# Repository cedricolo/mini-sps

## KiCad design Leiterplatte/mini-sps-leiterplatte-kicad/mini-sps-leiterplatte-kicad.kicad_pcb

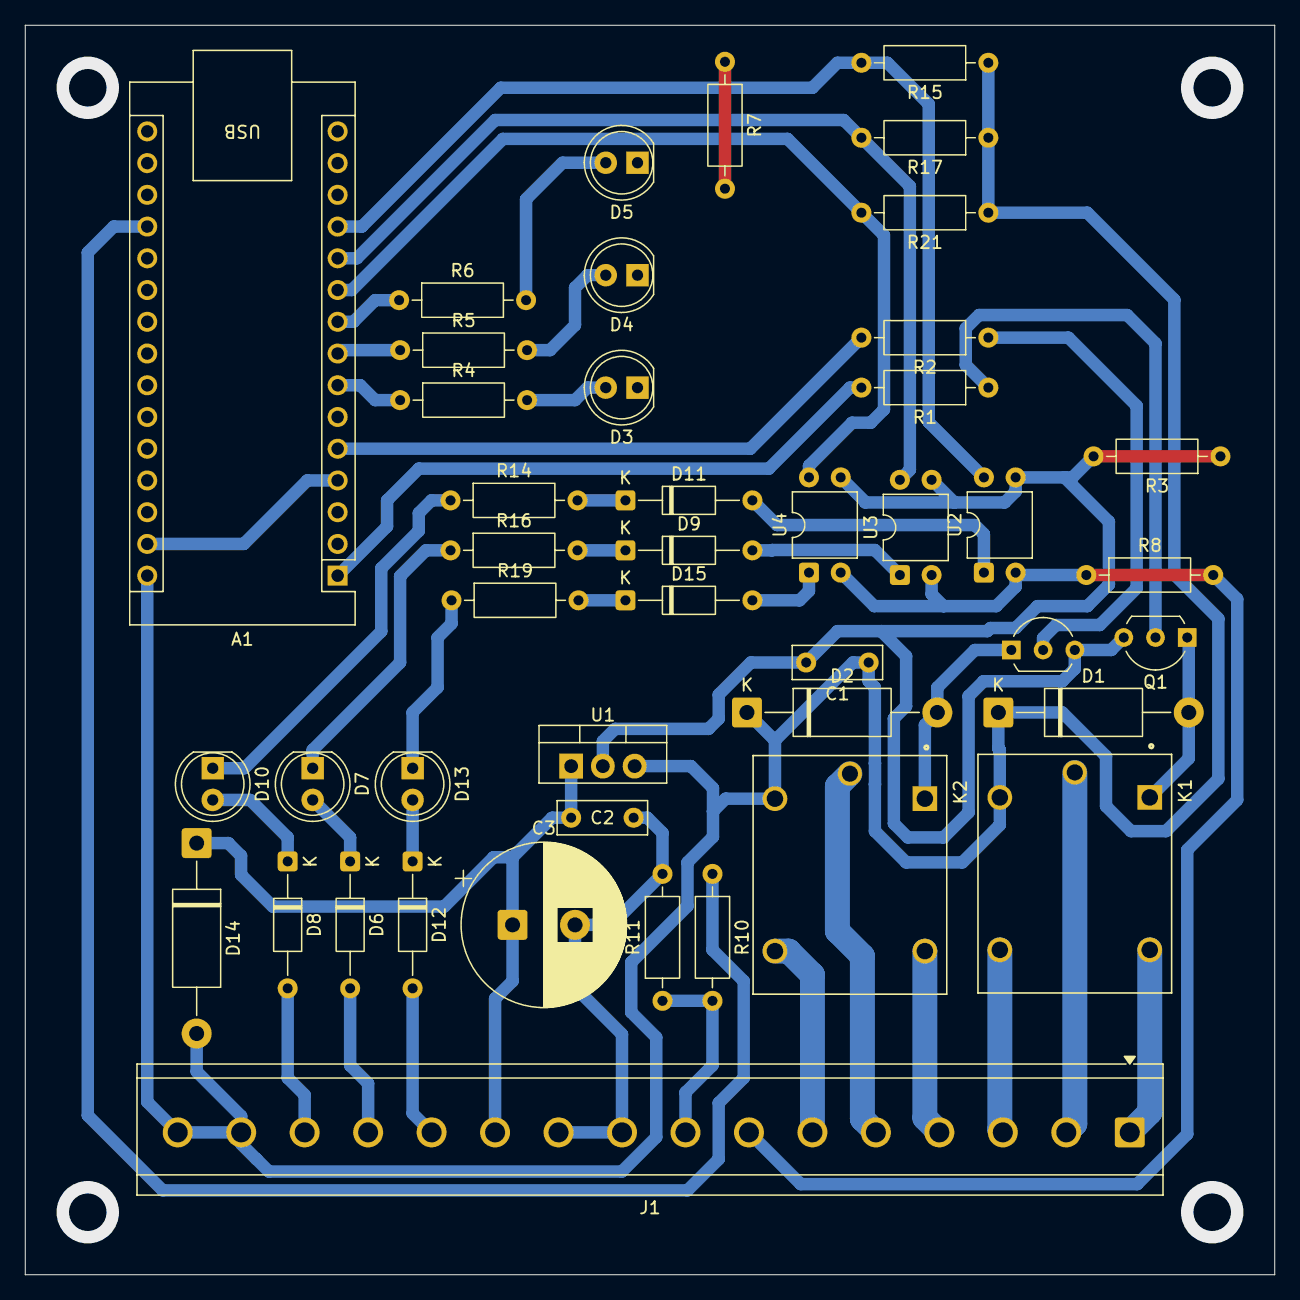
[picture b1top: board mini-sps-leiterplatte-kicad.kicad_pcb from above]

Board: 2 copper layers, 100.0 x 100.0 mm, 44 parts (0 on the bottom side), 42 nets.

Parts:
A1: Arduino_Nano_v3.x; Arduino_Nano
C1: 100nF; C_Disc_D7.0mm_W2.5mm_P5.00mm
C2: 330 nF; C_Disc_D7.0mm_W2.5mm_P5.00mm
C3: 10uF; CP_Radial_D13.0mm_P5.00mm
D1, D2, D14: 1N4007; D_DO-15_P15.24mm_Horizontal
D3, D4, D5, D7, D10, D13: LED; LED_D5.0mm
D6, D8, D12: 1N4148WT; D_DO-35_SOD27_P10.16mm_Horizontal
D9, D11, D15: BZV55B5V1; D_DO-35_SOD27_P10.16mm_Horizontal
J1: Screw_Terminal_01x16; TerminalBlock_CUI_TB007-508-16_1x16_P5.08mm_Horizontal
K1, K2: SRD-05VDC-SL-C; RELAY_SRD-05VDC-SL-C
Q1, Q2: BC547; TO-92L_Inline_Wide
R1, R2: 1k; R_Axial_DIN0207_L6.3mm_D2.5mm_P10.16mm_Horizontal
R3, R7, R8: 0; R_Axial_DIN0207_L6.3mm_D2.5mm_P10.16mm_Horizontal
R4, R5, R6: 330; R_Axial_DIN0207_L6.3mm_D2.5mm_P10.16mm_Horizontal
R10: 39k; R_Axial_DIN0207_L6.3mm_D2.5mm_P10.16mm_Horizontal
R11, R15, R17, R21: 10k; R_Axial_DIN0207_L6.3mm_D2.5mm_P10.16mm_Horizontal
R14, R16, R19: 1500; R_Axial_DIN0207_L6.3mm_D2.5mm_P10.16mm_Horizontal
U1: L7805; TO-220-3_Vertical
U2, U3, U4: PC817; DIP-4_W7.62mm

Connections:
+5V: A1.30 (VIN), C1.1, D1.1 (K), D2.1 (K), D14.2 (A), J1.15, J1.16, K1.A2, K2.A2, R15.1, R17.1, R21.1, U1.3 (OUT)
A0: A1.19 (A0), R10.1
AIN 1: J1.8, R10.2, R11.1
COM1: J1.2, K1.COM
COM2: J1.5, K2.COM
D1: A1.1 (D1/TX), R1.2
D2: A1.5 (D2), R2.2
D4(R): A1.7 (D4), R4.1
D5(G): A1.8 (D5), R5.1
D6(B): A1.9 (D6), R6.1
D7: A1.10 (D7), R21.2, U4.4
D8: A1.11 (D8), R17.2, U3.4
D9: A1.12 (D9), R15.2, U2.4
DI1: D12.2 (A), J1.12
DI2: D6.2 (A), J1.13
DI3: D8.2 (A), J1.14
GND: A1.4 (GND), A1.29 (GND), C1.2, C2.2, C3.2, D3.1 (K), D4.1 (K), D5.1 (K), J1.9, J1.10, Q1.3 (E), Q2.3 (E), R3.1, R3.2, R7.1, R7.2, R11.2, U1.2 (GND), U2.3, U3.3, U4.3
GND1: J1.7, R8.1, R8.2, U2.2, U3.2, U4.2
NC 1: J1.1, K1.NC
NC 2: J1.4, K2.NC
NO 1: J1.3, K1.NO
NO 2: J1.6, K2.NO
unnamed: D1.2 (A), K1.A1, Q1.1 (C)
unnamed: D2.2 (A), K2.A1, Q2.1 (C)
unnamed: D3.2 (A), R4.2
unnamed: D4.2 (A), R5.2
unnamed: D5.2 (A), R6.2
unnamed: D6.1 (K), D7.2 (A)
unnamed: D7.1 (K), R16.1
unnamed: D9.2 (A), U3.1
unnamed: D9.1 (K), R16.2
unnamed: D8.1 (K), D10.2 (A)
unnamed: D10.1 (K), R14.1
unnamed: D11.2 (A), U2.1
unnamed: D11.1 (K), R14.2
unnamed: D12.1 (K), D13.2 (A)
unnamed: D13.1 (K), R19.1
unnamed: D15.2 (A), U4.1
unnamed: D15.1 (K), R19.2
unnamed: Q1.2 (B), R1.1
unnamed: Q2.2 (B), R2.1
Vin: C2.1, C3.1, D14.1 (K), J1.11, U1.1 (IN)

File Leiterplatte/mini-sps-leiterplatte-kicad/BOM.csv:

"Reference","Qty","Value","DNP","Exclude from BOM","Exclude from Board","Footprint","Datasheet"
"A1","1","Arduino_Nano_v3.x","","","","Module:Arduino_Nano","http://www.mouser.com/pdfdocs/Gravitech_Arduino_Nano3_0.pdf"
"C1","1","100nF","","","","Capacitor_THT:C_Disc_D7.0mm_W2.5mm_P5.00mm","~"
"C2","1","330 nF","","","","Capacitor_THT:C_Disc_D7.0mm_W2.5mm_P5.00mm","~"
"C3","1","10uF","","","","Capacitor_THT:CP_Radial_D13.0mm_P5.00mm","~"
"D1,D2,D14","3","1N4007","","","","Diode_THT:D_DO-15_P15.24mm_Horizontal","~"
"D3,D4,D5,D7,D10,D13","6","LED","","","","LED_THT:LED_D5.0mm","~"
"D6,D8,D12","3","1N4148WT","","","","Diode_THT:D_DO-35_SOD27_P10.16mm_Horizontal","https://www.diodes.com/assets/Datasheets/ds30396.pdf"
"D9,D11,D15","3","BZV55B5V1","","","","Diode_THT:D_DO-35_SOD27_P10.16mm_Horizontal","https://assets.nexperia.com/documents/data-sheet/BZV55_SER.pdf"
"J1","1","Screw_Terminal_01x16","","","","TerminalBlock_CUI:TerminalBlock_CUI_TB007-508-16_1x16_P5.08mm_Horizontal","~"
"K1,K2","2","SRD-05VDC-SL-C","","","","relay:RELAY_SRD-05VDC-SL-C",""
"Q1,Q2","2","BC547","","","","Package_TO_SOT_THT:TO-92L_Inline_Wide","https://www.onsemi.com/pub/Collateral/BC550-D.pdf"
"R0,R3,R7,R8,R9","5","0","","","","Resistor_THT:R_Axial_DIN0207_L6.3mm_D2.5mm_P10.16mm_Horizontal","~"
"R1,R2","2","1k","","","","Resistor_THT:R_Axial_DIN0207_L6.3mm_D2.5mm_P10.16mm_Horizontal","~"
"R4,R5,R6","3","330","","","","Resistor_THT:R_Axial_DIN0207_L6.3mm_D2.5mm_P10.16mm_Horizontal","~"
"R10","1","39k","","","","Resistor_THT:R_Axial_DIN0207_L6.3mm_D2.5mm_P10.16mm_Horizontal","~"
"R11,R15,R17,R21","4","10k","","","","Resistor_THT:R_Axial_DIN0207_L6.3mm_D2.5mm_P10.16mm_Horizontal","~"
"R14,R16,R19","3","1500","","","","Resistor_THT:R_Axial_DIN0207_L6.3mm_D2.5mm_P10.16mm_Horizontal","~"
"U1","1","L7805","","","","Package_TO_SOT_THT:TO-220-3_Vertical","http://www.st.com/content/ccc/resource/technical/document/da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"
"U2,U3,U4","3","PC817","","","","Package_DIP:DIP-4_W7.62mm","http://www.soselectronic.cz/a_info/resource/d/pc817.pdf"

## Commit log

2026-01-27 v.1(Relais un LED
2026-01-27 v.2 schreubdinger
2026-02-04 v.3 Spannungsversorgung etc
2026-02-05 v.4 footprints):
2026-04-05 alles auf den neusten fucking stand
2026-04-05 alles neu diggi
2026-04-05 fertig lk
2026-04-09 version 2
2026-04-10 dedee
